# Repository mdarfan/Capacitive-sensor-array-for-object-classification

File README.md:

# Capacitive-sensor-array-for-object-classification
1. Make sure you have the following libraries in python installed
	1. pyserial
	2. tensorflow
	3. numpy
2. handSese_ML_ref
	This contains the reference code for the sensor. It has three modes f operation
	1. Looks and continuously prints data of a single pixel. different pixels can be selected using the commane
		"Space" m x y (for looking at pixel x,y)
	2. Calibration This mode calibrated the array by getting channel Multiplexers. This mode can be accessed by pressing "2"
	3. Scan This scans the entire array and prints the normalised value. This can be accessed by pressing 3
3. hanSense_data_acq
	This file is used for getting data for the ML. run this file and press "2" to calibrate.
	Then press 3 to scan the array 10 times and the results are stored in file.csv.
	Add an extra column in fie.csv and lable the data accordingly to get data.csv
4. NN_model.py
	This is used to train and create the neural network.
	Make sure all the data.csv is present in proper format (36 pixels values and 1 labels column).
	This saves the model and dictionary in model folder
5. handSense_ML
	This has two modes. Make sure model and dictionary.csv are resent before running
	press 2 to calibrate
	press 3 to scan and classify the object.
6. EAGLE
	This contains the schematic and PCB of the system PCB that cen be opened and edited in eagle.

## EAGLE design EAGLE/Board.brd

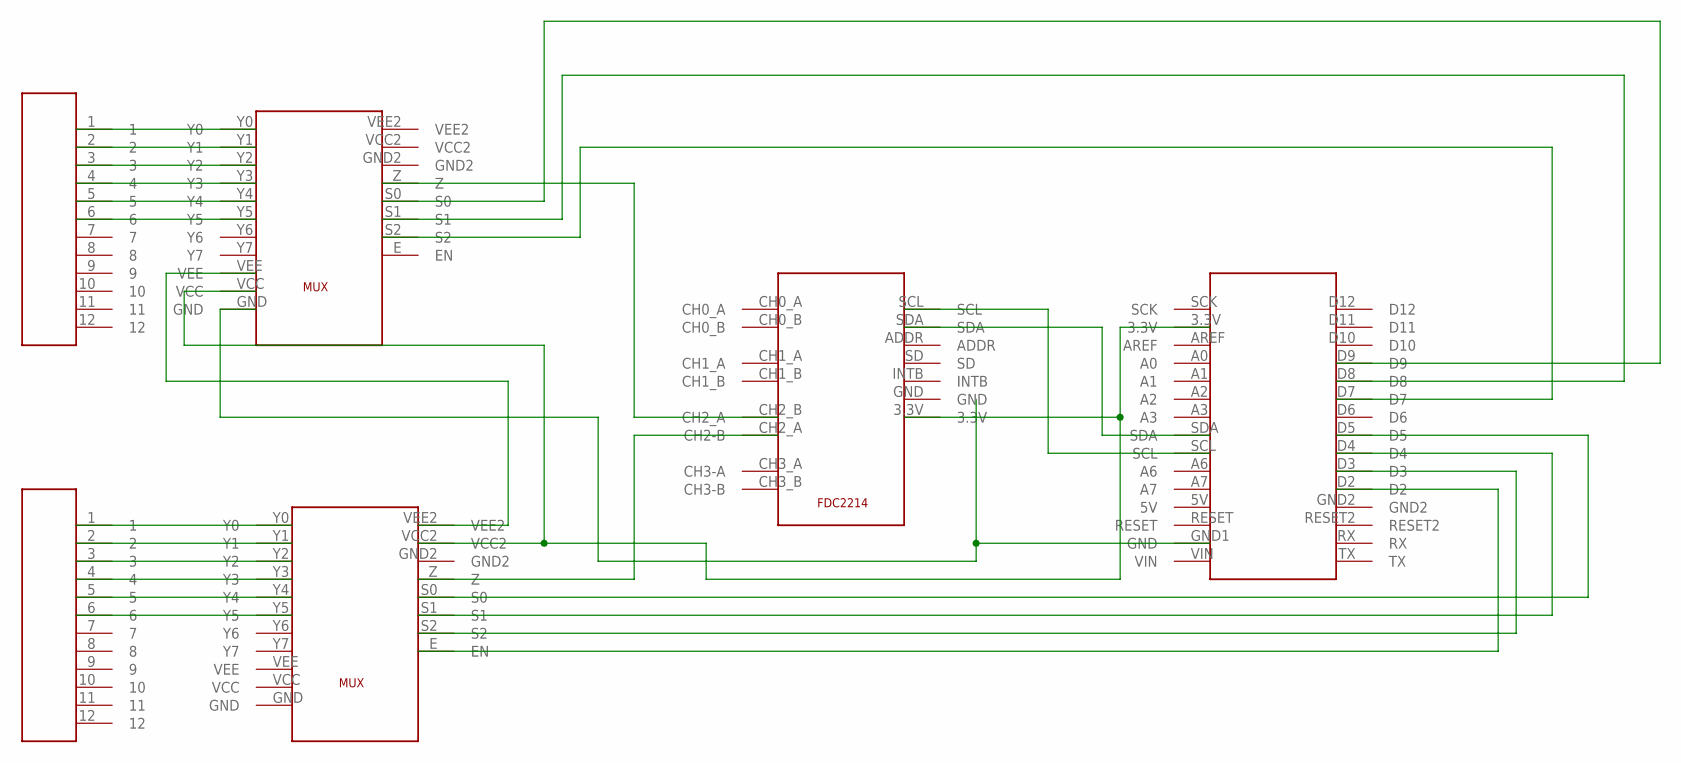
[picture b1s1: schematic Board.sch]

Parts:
U$1: BLE33BLE33; BLE33
U$2, U$3: MUXMUX; MUX
U$4, U$5: MOLEXMOLEX; MOLEX
U$6: FDC2214FDC2214; FDC2214

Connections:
unnamed: U$2.Y0, U$4.1
unnamed: U$2.Y1, U$4.2
unnamed: U$2.Y2, U$4.3
unnamed: U$2.Y3, U$4.4
unnamed: U$2.Y4, U$4.5
unnamed: U$2.Y5, U$4.6
unnamed: U$3.Y0, U$5.1
unnamed: U$3.Y1, U$5.2
unnamed: U$3.Y2, U$5.3
unnamed: U$3.Y3, U$5.4
unnamed: U$3.Y4, U$5.5
unnamed: U$3.Y5, U$5.6
unnamed: U$3.Z, U$6.CH2_A (CH2-B)
unnamed: U$2.Z, U$6.CH2_B (CH2_A)
unnamed: U$1.SCL, U$6.SCL
unnamed: U$1.SDA, U$6.SDA
unnamed: U$1.D2, U$3.E (EN)
unnamed: U$1.D3, U$3.S2
unnamed: U$1.3.3V, U$2.VCC, U$3.VCC2, U$6.3.3V
unnamed: U$1.D4, U$3.S1
unnamed: U$1.D5, U$3.S0
unnamed: U$1.D7, U$2.S2
unnamed: U$1.D8, U$2.S1
unnamed: U$1.D9, U$2.S0
unnamed: U$2.VEE, U$3.VEE2
unnamed: U$1.GND1 (GND), U$2.GND, U$3.GND2, U$6.GND

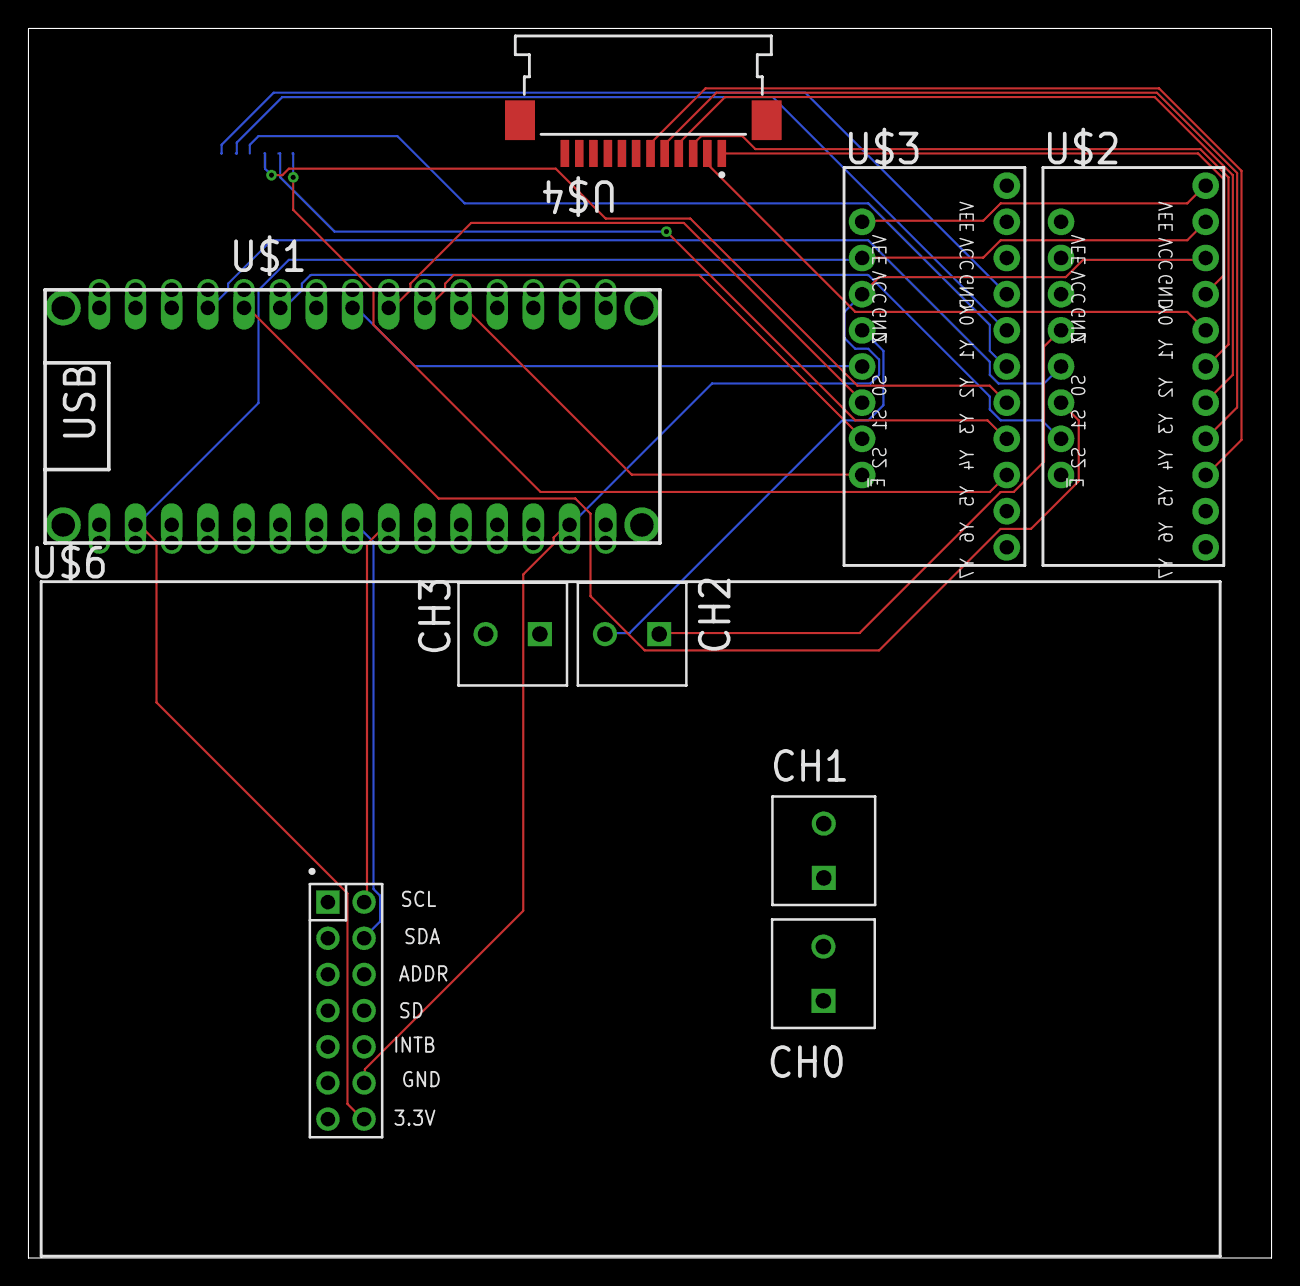
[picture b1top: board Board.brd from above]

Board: 2 copper layers, 87.3 x 86.3 mm, 6 parts (1 on the bottom side), 26 nets.
